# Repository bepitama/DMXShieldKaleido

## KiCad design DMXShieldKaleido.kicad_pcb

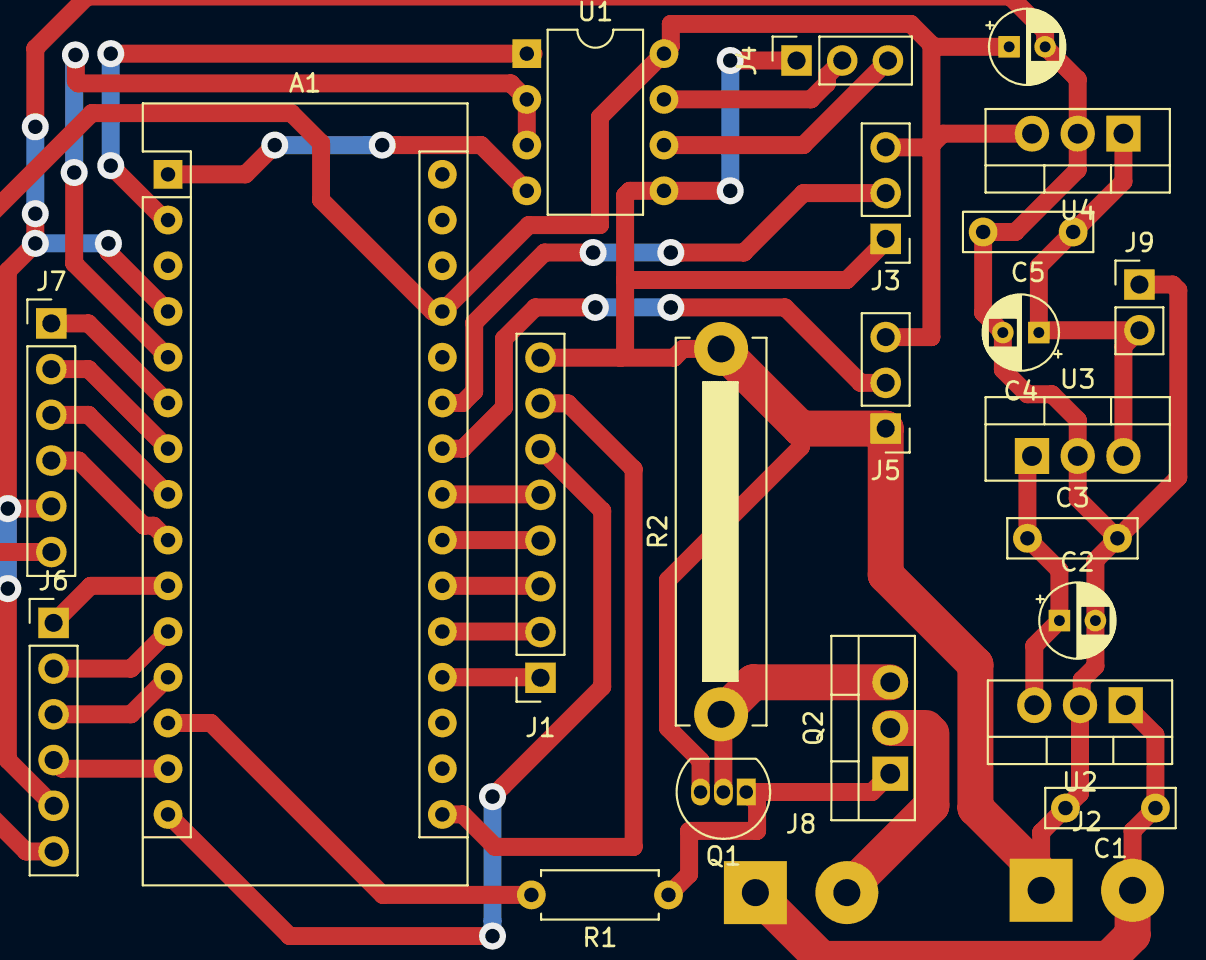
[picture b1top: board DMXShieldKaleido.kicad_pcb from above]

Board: 2 copper layers, 24 parts (0 on the bottom side), 31 nets.

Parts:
A1: Arduino_Nano_v3.x; Arduino_Nano
C1, C3, C5: C; C_Rect_L7.0mm_W2.0mm_P5.00mm
C2, C4, C6: CP; CP_Radial_D4.0mm_P2.00mm
J1: DMXChannelSelect; PinSocket_1x08_P2.54mm_Vertical
J2: Power 30V; SolderWirePad_1x02_P5.08mm_Drill1.5mm
J3: EndStop2; PinHeader_1x03_P2.54mm_Vertical
J4: DMX; PinSocket_1x03_P2.54mm_Vertical
J5: EndStop1; PinHeader_1x03_P2.54mm_Vertical
J6: Motor2; PinHeader_1x06_P2.54mm_Vertical
J7: Motor1; PinHeader_1x06_P2.54mm_Vertical
J8: LED; SolderWirePad_1x02_P5.08mm_Drill1.5mm
J9: Fan; PinHeader_1x02_P2.54mm_Vertical
Q1: BC547; TO-92_Inline
Q2: Q_NMOS_GDS; TO-220-3_Vertical
R1: 10K; R_Axial_DIN0207_L6.3mm_D2.5mm_P7.62mm_Horizontal
R2: 0,33; R_Bare_Metal_Element_L21.3mm_W4.8mm_P20.30mm
U1: SP3485CN; DIP-8_W7.62mm
U2: L7824; TO-220-3_Vertical
U3: L7812; TO-220-3_Vertical
U4: L7805; TO-220-3_Vertical

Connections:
unnamed: A1.1, U1.4
unnamed: A1.2, U1.1
unnamed: A1.4, C1.2, C2.2, C3.2, C4.2, C5.2, C6.2, J1.8, J2.1, J3.1, J4.1, J5.1, J6.5, J7.5, J9.1, Q1.3, R2.2, U1.5, U2.2, U3.2, U4.2
unnamed: A1.5, U1.2, U1.3
unnamed: A1.6, J7.1
unnamed: A1.7, J7.2
unnamed: A1.8, J7.3
unnamed: A1.9, J7.4
unnamed: A1.10, J6.1
unnamed: A1.11, J6.2
unnamed: A1.12, J6.3
unnamed: A1.13, R1.2
unnamed: A1.14, J6.4
unnamed: A1.15, J1.6
unnamed: A1.16, J1.7
unnamed: A1.19, J1.1
unnamed: A1.20, J1.2
unnamed: A1.21, J1.3
unnamed: A1.22, J1.4
unnamed: A1.23, J1.5
unnamed: A1.24, J5.2
unnamed: A1.25, J3.2
unnamed: A1.27, C6.1, J3.3, J5.3, J6.6, J7.6, U1.8, U4.3
unnamed: C1.1, J2.2, J8.1, U2.1
unnamed: C2.1, C3.1, U2.3, U3.1
unnamed: C4.1, C5.1, J9.2, U3.3, U4.1
unnamed: J4.2, U1.7
unnamed: J4.3, U1.6
unnamed: J8.2, Q2.2
unnamed: Q1.1, Q2.1, R1.1
unnamed: Q1.2, Q2.3, R2.1
